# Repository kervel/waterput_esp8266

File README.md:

# About

This is a simple breakout for an ESP12MOD module that enables easy connection to a 5V power supply and that converts 2 IOs to 5V levels, suitable for connecting an acoustic waterlevel sensor.

The software reads the acoustic waterlevel sensor 30 times and sends the median value via MQTT.

# The hardware

Following components are needed:
* the pcb's (Aisler template is used in pcb/ folder, so easiest to order via aisler)
* an ESP12MOD module (the one with 22 pins!)
* A SR04M-2 acoustic sensor or equivalent
* A LM1117T linear regulator in a TO-220-3 package
* 8 10Kohm 0805 resistors
* 2 BSS138 mosfets in SOT-23 package
* A screw terminal block with 2 connections pitch 3.5mm
* A 0.1μF radial electrolytic capacitor, diameter 4mm, pitch 2mm
* 2 10μF radial electrolytic capacitors, diameter 4mm, pitch 2mm
* female pin header, 6 pins, 2.54mm pitch
* male pin header, 4 pins, 2.54mm pitch for reset/program jumper (optional)
* a jumper or a jumper cable (optional)

To connect the acoustic sensor, note that the `TRG` pin might be called `RX`
and the `ECHO` pin might be called `TX`. This is because some boards can be
configured to operate in serial mode by adding a resistor.

# Uploading the firmware

Use platformIO to build it. To upload it, ground the "PRG" pin on the board by connecting a jumper between the PRG and the GND pins, and connect a FTDI module to the female pin header (check the pin-out: 5V must match 5V and GND must match GND, and RX of the board must be connected with TX of the FTDI and vice versa).

After connecting the module, uploading the software should be possible with control-shift-P

# Configuring the firmware

Unplug the programming jumper and supply 5V or connect the FTDI again (the PCB can take power from the FTDI, but make sure to unplug/replug to trigger a reboot after programming). Now an access point should become availabe. Connect to it with your android phone, a web interface will pop up where you can set the wifi parameters and the mqtt server.

Write down the chip ID (which is equal to the access point name). After configuration is done the chip will connect to the MQTT server and it will publish some topics:

* `/[chip_id]/online` will contain the number of iterations since boot-up, or will equal "0" if the module is offline
* `/[chip_id]/state` will contain the distance

Every time information is sent to MQTT, the LED will flash briefly 3 times.

# Firmware factory reset

Power up the firmware, and *while powered up* connect a jumper between PRG and GND pins. The blue LED will immediately blink 10 times and all settings will be cleared.
Note that this *will not work* if you already connect the jumper cable
before powerup, because then the board will enter firmware download mode.

# Data logging on kubernetes

The k8s subdirectory contains resources for:
* a MQTT server
* influxdb
* telegraf configured to log everything from the MQTT server to influxdb
* grafana

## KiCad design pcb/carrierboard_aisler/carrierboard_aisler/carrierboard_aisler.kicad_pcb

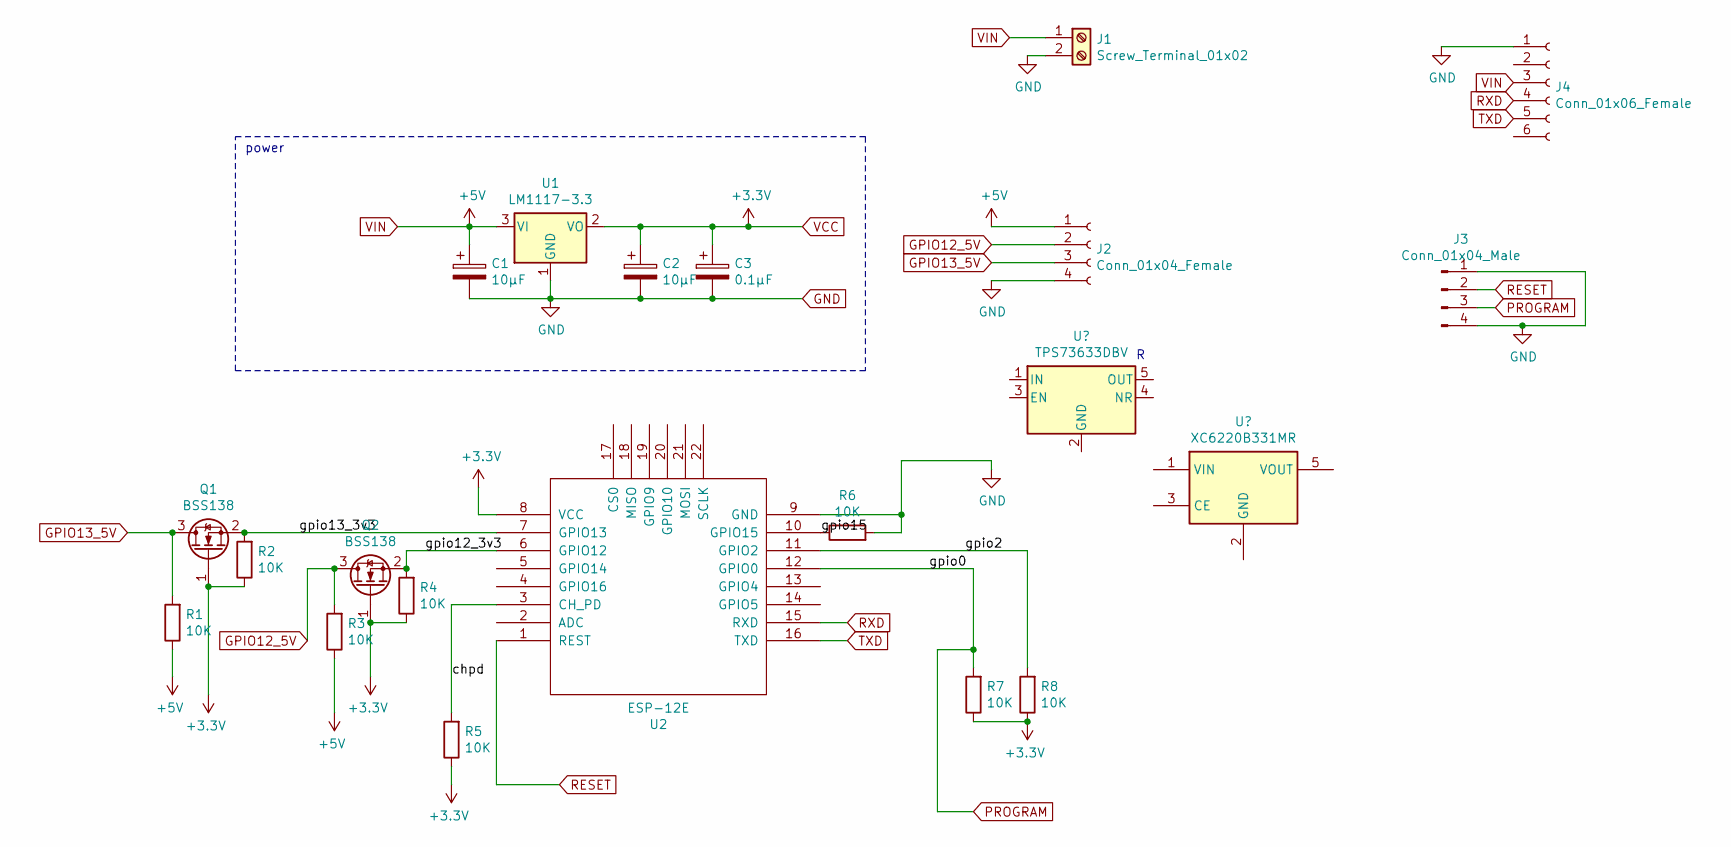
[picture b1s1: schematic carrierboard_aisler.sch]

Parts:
C1, C2: 10μF; CP_Radial_D4.0mm_P2.00mm
C3: 0.1μF; CP_Radial_D4.0mm_P2.00mm
J1: Screw_Terminal_01x02; TerminalBlock_4Ucon_1x02_P3.50mm_Vertical
J2: Conn_01x04_Female; PinHeader_1x04_P2.54mm_Vertical
J3: Conn_01x04_Male; PinHeader_1x04_P2.54mm_Vertical
J4: Conn_01x06_Female; PinHeader_1x06_P2.54mm_Vertical
Q1, Q2: BSS138; SOT-23
R1, R2, R3, R4, R5, R6, R7, R8: 10K; R_0805_2012Metric_Pad1.15x1.40mm_HandSolder
U1: LM1117-3.3; TO-220-3_Vertical
U2: ESP-12E; ESP-12E_SMD

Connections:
/chpd: R5.2, U2.3 (CH_PD)
/gpio2: R8.2, U2.11 (GPIO2)
/gpio12_3v3: Q2.2 (S), R4.2, U2.6 (GPIO12)
/gpio13_3v3: Q1.2 (S), R2.2, U2.7 (GPIO13)
/gpio15: R6.1, U2.10 (GPIO15)
GND: C1.2, C2.2, C3.2, J1.2, J2.4, J3.1, J3.4, J4.1, R6.2, U1.1 (GND), U2.9 (GND)
GPIO12_5V: J2.2, Q2.3 (D), R3.2
GPIO13_5V: J2.3, Q1.3 (D), R1.2
PROGRAM: J3.3, R7.2, U2.12 (GPIO0)
RESET: J3.2, U2.1 (REST)
RXD: J4.4, U2.15 (RXD)
TXD: J4.5, U2.16 (TXD)
VCC: C2.1, C3.1, Q1.1 (G), Q2.1 (G), R2.1, R4.1, R5.1, R7.1, R8.1, U1.2 (VO), U2.8 (VCC)
VIN: C1.1, J1.1, J2.1, J4.3, R1.1, R3.1, U1.3 (VI)

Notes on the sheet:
power

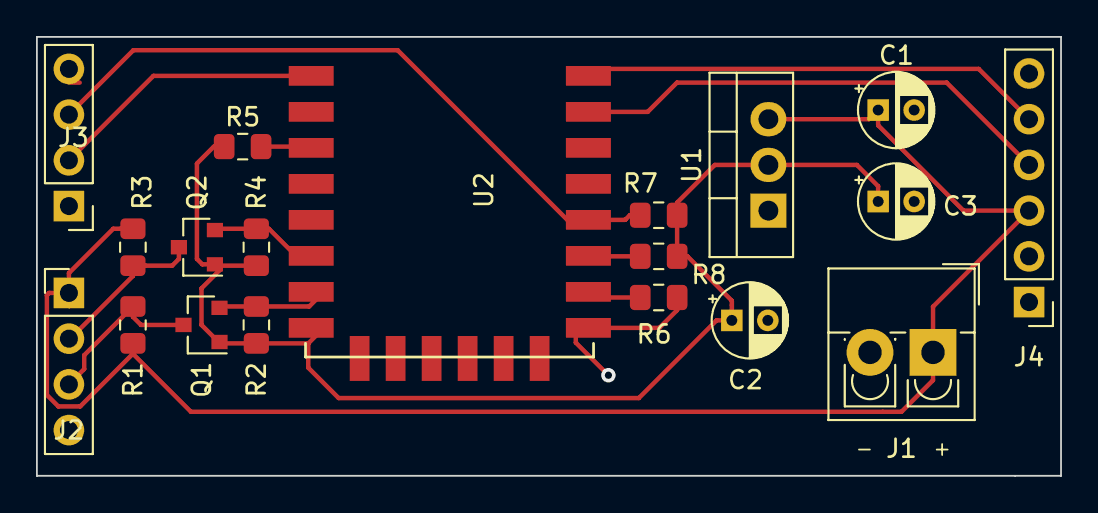
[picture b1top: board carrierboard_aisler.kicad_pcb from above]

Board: 2 copper layers, 56.9 x 24.4 mm, 19 parts (0 on the bottom side), 14 nets.

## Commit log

2020-08-18 try to be less noisy
2020-08-18 remov
2020-08-26 wifi manager
2020-08-26 okay
2020-08-26 explicit dependencies
2020-08-26 add readme
2020-08-26 pics
2020-08-26 more info
2020-08-27 basic CI
2020-08-27 add versions
2020-08-27 artifacts
2020-08-27 datasheet
2020-08-27 screenshots
2020-08-28 add gitignore
2021-04-11 fix sending the password to mqtt server
